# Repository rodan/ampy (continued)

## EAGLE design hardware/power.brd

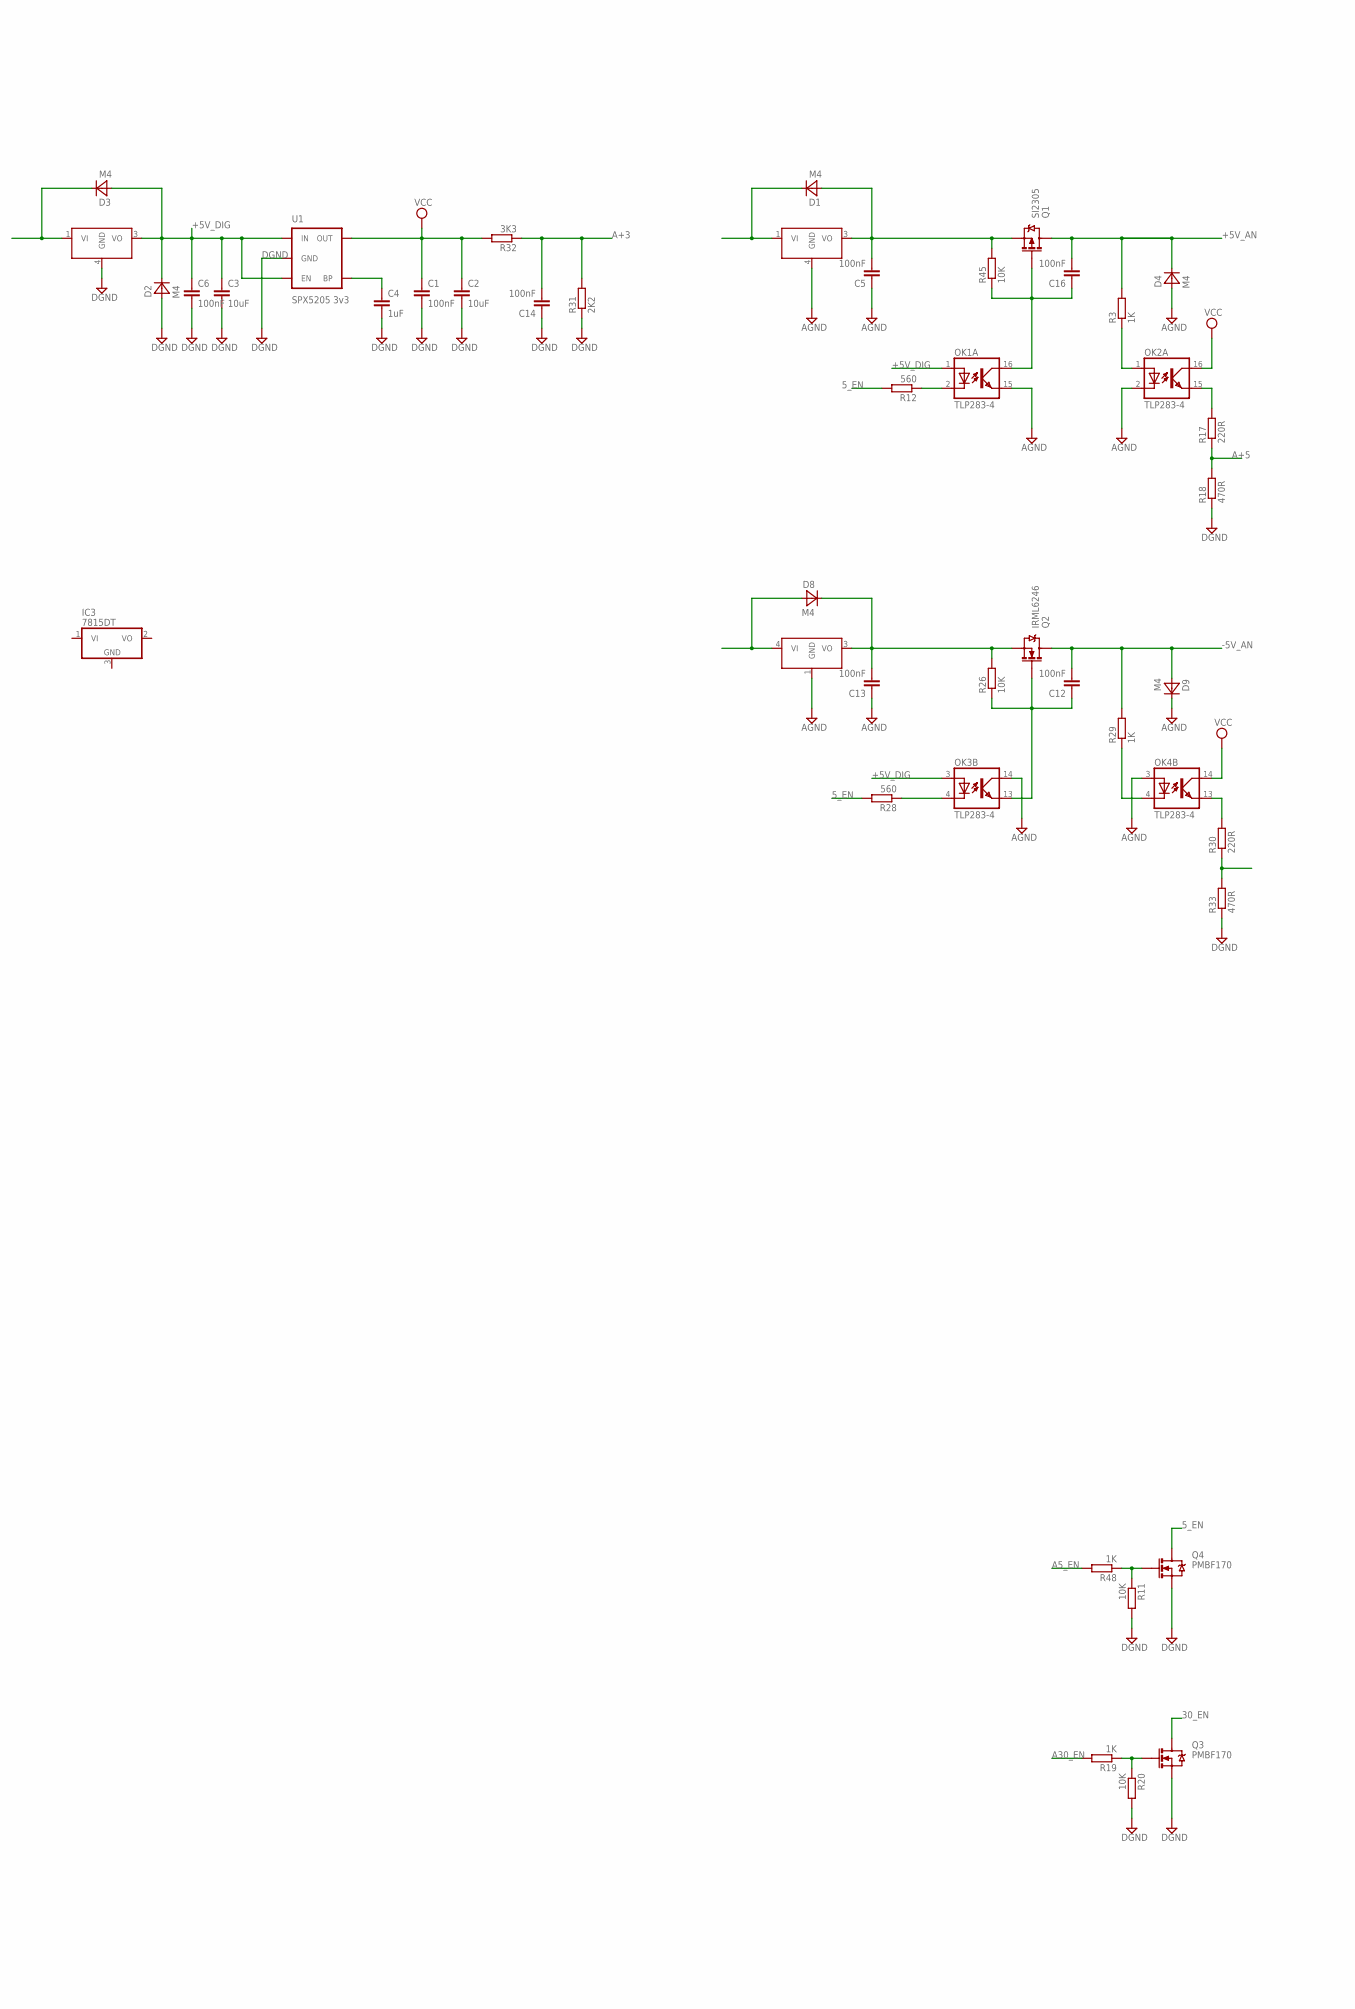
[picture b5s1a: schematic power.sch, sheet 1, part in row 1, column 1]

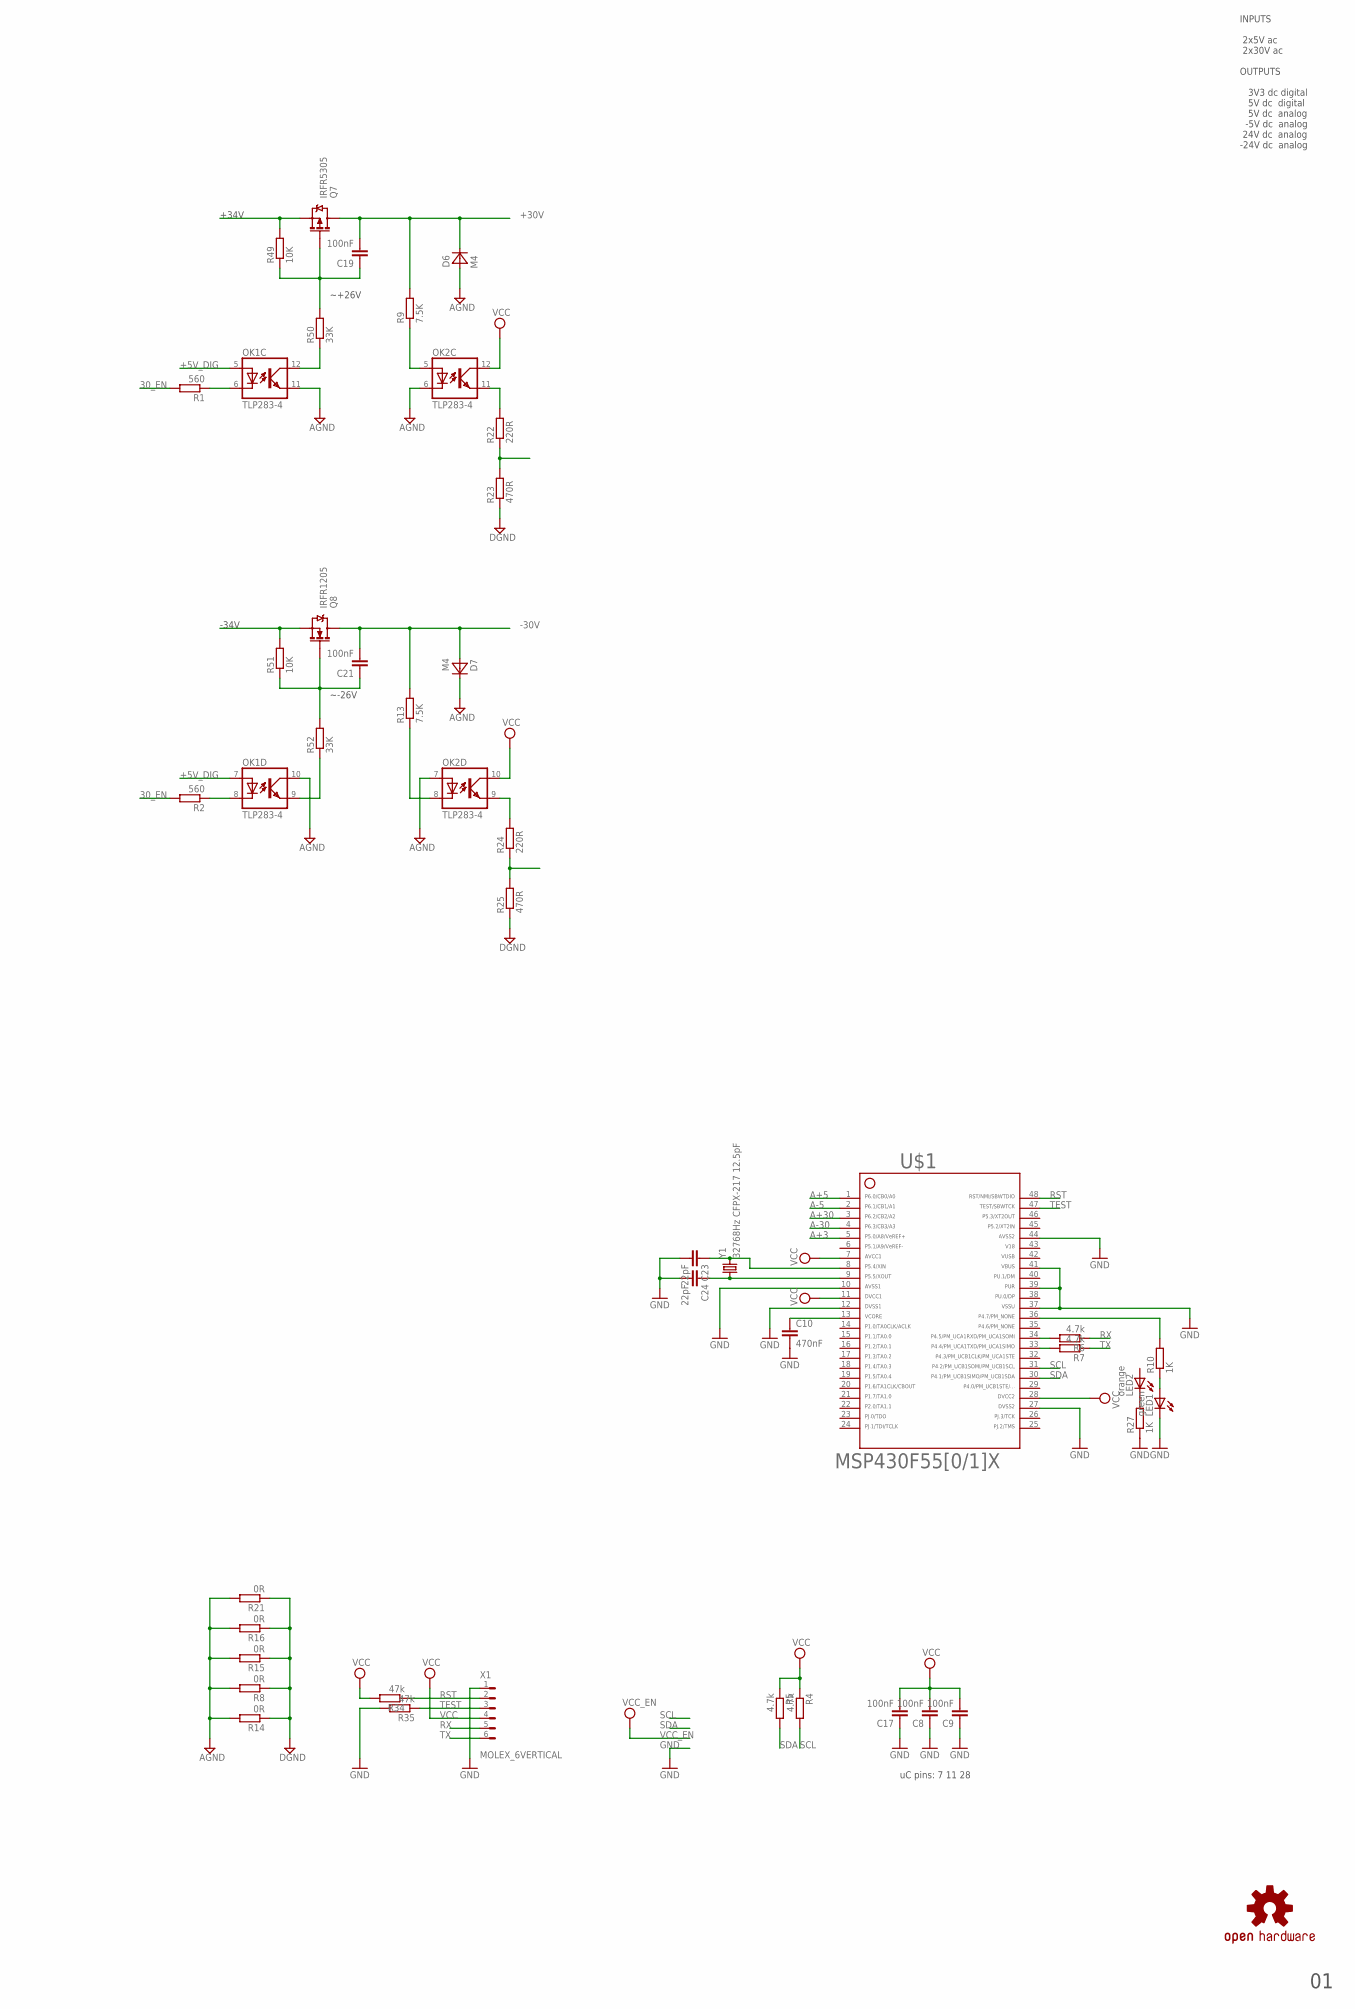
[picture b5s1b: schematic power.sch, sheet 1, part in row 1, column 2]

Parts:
C1, C5, C6, C8, C9, C12, C13, C14, C16, C17, C19, C21: 100nF; C0805
C2, C3: 10uF; C1206
C4: 1uF; C0805
C10: 470nF; C0805
C23, C24: 22pF; C0805
D1, D2, D3, D4, D6, D7, D8, D9: M4; SMA
IC1, IC2: 7805; D2PACK
IC3: 7815DT; TO252
IC4: 7905; D2PACK
LED1: green; CHIP-LED0805
LED2: orange; CHIP-LED0805
OK1, OK2, OK3, OK4: TLP283-4; MINI-FLAT-16
Q1: SI2305; SOT23-3_POWER
Q2: IRML6246; SOT23-3_POWER
Q3, Q4: PMBF170; SOT23-3
Q7: IRFR5305; D-PAK_TO252AA
Q8: IRFR1205; D-PAK_TO252AA
R1, R2, R12, R28: 560; R0805W
R3, R10, R19, R27, R29, R48: 1K; R0805W
R4, R5, R6, R7: 4.7k; R0805W
R8, R14, R15, R16, R21: 0R; R0805W
R9, R13: 7.5K; R0805W
R11, R20, R26, R45, R49, R51: 10K; R0805W
R17, R22, R24, R30: 220R; R0805W
R18, R23, R25, R33: 470R; R0805W
R31: 2K2; R0805W
R32: 3K3; R0805W
R34, R35: 47k; R0805W
R50, R52: 33K; R0805W
U1: SPX5205 3v3; SOT23-5
U$1: F55[0/1]X---PT48; PT48
U$7: OSHW-LOGOM; OSHW-LOGO-M
X1: MOLEX_6VERTICAL; 0530470610
Y1: 32768Hz CFPX-217 12.5pF; CRYSTAL-SMD-3.2X1.5

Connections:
5_EN: Q4.3 (D), R12.2, R28.2
30_EN: Q3.3 (D), R1.2, R2.2
42: U$1.42
43: U$1.43
46: U$1.46
$N2: C13.2, D8.C, IC4.3 (VO), Q2.2 (S), R26.2
$N333: C5.2, D1.A, IC1.3 (VO), Q1.2 (S), R45.2
+5V_AN: C16.2, D4.C, Q1.3 (D), R3.2
+5V_DIG: C3.1, C6.1, D2.C, D3.A, IC2.3 (VO), OK1.1 (A), OK1.5 (A), OK1.7 (A), OK3.3 (A), U1.1 (IN), U1.3 (EN)
+30V: C19.2, D6.C, Q7.2 (D), R9.2
-5V_AN: C12.2, D9.A, Q2.3 (D), R29.2
-30V: C21.2, D7.A, Q8.2 (D), R13.2
A5_EN: R48.2
A30_EN: R19.2
A+3: C14.2, R31.2, R32.1, U$1.5
A+5: R17.1, R18.2, U$1.1
A+30: U$1.3
A-5: U$1.2
A-30: U$1.4
AGND: C5.1, C13.1, D4.A, D6.A, D7.C, D9.C, IC1.4 (GND), IC4.1 (GND), OK1.10 (COL), OK1.11 (EMIT), OK1.15 (EMIT), OK2.2 (C), OK2.6 (C), OK2.7 (A), OK3.14 (COL), OK4.3 (A), R8.2, R14.2, R15.2, R16.2, R21.2
DGND: C1.2, C2.2, C3.2, C4.2, C6.2, C14.1, D2.A, IC2.4 (GND), Q3.2 (S), Q4.2 (S), R8.1, R11.2, R14.1, R15.1, R16.1, R18.1, R20.2, R21.1, R23.1, R25.1, R31.1, R33.1, U1.2 (GND)
GND: C8.1, C9.1, C10.2, C17.1, C23.2, C24.2, LED1.C, R27.1, R35.2, U$1.10, U$1.12, U$1.27, U$1.37, U$1.39, U$1.41, U$1.44, X1.1
LED: R10.2, U$1.36
unnamed: LED1.A, R10.1
unnamed: C4.1, U1.4 (BP)
unnamed: D1.C, IC1.1 (VI)
unnamed: Q4.1 (G), R11.1, R48.1
unnamed: C10.1, U$1.13
unnamed: OK1.2 (C), R12.1
unnamed: OK1.8 (C), R2.1
unnamed: R6.2, U$1.34
unnamed: OK2.1 (A), R3.1
unnamed: R7.2, U$1.33
unnamed: OK2.5 (A), R9.1
unnamed: OK2.8 (C), R13.1
unnamed: Q3.1 (G), R19.1, R20.1
unnamed: OK1.6 (C), R1.1
unnamed: D3.C, IC2.1 (VI)
unnamed: OK2.15 (EMIT), R17.2
unnamed: C12.1, OK3.13 (EMIT), Q2.1 (G), R26.1
unnamed: C24.1, U$1.9, Y1.P$1 (1)
unnamed: C23.1, U$1.8, Y1.P$2 (2)
unnamed: OK2.11 (EMIT), R22.2
unnamed: R22.1, R23.2
unnamed: OK2.9 (EMIT), R24.2
unnamed: R24.1, R25.2
unnamed: D8.A, IC4.4 (VI)
unnamed: OK3.4 (C), R28.1
unnamed: OK4.4 (C), R29.1
unnamed: OK4.13 (EMIT), R30.2
unnamed: R30.1, R33.2
unnamed: C16.1, OK1.16 (COL), Q1.1 (G), R45.1
unnamed: LED2.C, R27.2
unnamed: Q7.3 (S), R49.2
unnamed: C19.1, Q7.1 (G), R49.1, R50.2
unnamed: OK1.12 (COL), R50.1
unnamed: Q8.3 (S), R51.2
unnamed: C21.1, Q8.1 (G), R51.1, R52.2
unnamed: OK1.9 (EMIT), R52.1
RST: R34.1, U$1.48, X1.2
RX: R6.1, X1.5
SCL: R4.2, U$1.31
SDA: R5.2, U$1.30
TEST: R35.1, U$1.47, X1.3
TX: R7.1, X1.6
VCC: C1.1, C2.1, C8.2, C9.2, C17.2, OK2.10 (COL), OK2.12 (COL), OK2.16 (COL), OK4.14 (COL), R4.1, R5.1, R32.2, R34.2, U1.5 (OUT), U$1.7, U$1.11, U$1.28, X1.4

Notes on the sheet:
uC pins: 7 11 28
~+26V
+34V
~-26V
-34V
INPUTS 2x5V ac 2x30V ac OUTPUTS 3V3 dc digital 5V dc digital 5V dc analog -5V dc analog 24V dc analog -24V dc analog

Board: 2 copper layers, 88 parts (0 on the bottom side), 58 nets, no tracks yet.

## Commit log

2014-02-09 add png
2014-02-09 power tweaked
2014-02-09 add msp
2014-02-11 add power module
2014-02-11 cleanup
2014-02-15 change C footprints
2014-02-15 change input filters
2014-02-15 add jumper for pan input
2014-02-15 change input filters - agin
2014-02-16 started routing
2014-04-19 use 7905
2014-04-26 routing
2014-04-28 done routing the mixer
2014-04-28 add amp
2014-04-28 amp update
2014-05-02 amplifier schematic
2014-05-12 mosfets purchased
2014-05-13 amp routed
2014-05-14 add low voltage power source board
2014-05-15 add amp source board
2014-05-15 tweaks
2014-05-20 sent to manufacture
2014-06-02 tweak filters
2014-06-04 small tweaks
2014-06-07 add mixer firmware
2014-06-07 add README
2014-06-08 board rev 1.1
2014-06-08 change +5v bridge rectifier in power_pre
2014-06-15 add firmware for the main uC
2014-06-15 add i2c and uart interfaces
2014-06-16 works part1
2014-06-17 s/sprintf/snprintf/g
2014-06-18 code cleanup
2014-06-23 use non-blocking delays and LPM3
2014-07-03 add pic link
2014-07-03 add display firmware
2014-07-03 fix indent
2014-12-17 add pinout
2014-12-17 add UI, sound detection
2014-12-18 add debounce and timeouts for sound detection routine
2014-12-19 ir_isr tied in directly not thru the sys_messagebus
2014-12-19 remove ir debug
2014-12-19 new power amp
2014-12-20 switch to i2c bitbang, implelent clock stretching
2014-12-24 add linux client
2014-12-24 add ncurses
2014-12-28 borrow code from alsamixer
2014-12-28 borrow some more
2014-12-28 cleanup, fix for screen resize
2014-12-31 store_registers() added
2014-12-31 lm4780_helper added
2014-12-31 new year cleanup
2014-12-31 change labels
2015-01-02 add internal tty reconf and transmit buffers
2015-01-02 add autotools
2015-01-02 use compile time default stty
2015-01-02 add replies
2015-01-02 ampy_tx_cmd now expects the length of the reply
2015-01-03 move sources to src
2015-01-03 add gitignore
2015-01-03 flush file descriptor buffer before every new command
2015-01-04 automake added
2015-01-04 remove m4 dir dependency
2015-01-04 remove m4 dir dependency part2
2015-01-04 bootstrap updated
2015-01-04 add ebuild
2015-01-04 repoman fixes
2015-01-22 fix gnd_c in amp_lm4780
2015-01-23 add buffer to snd detect circuit
2015-01-27 spice simulation added
2015-01-27 redesign snd_detect circuit layout
2015-01-28 snd_detect cleanup
2015-01-29 snd_detect revisited
2015-02-12 add xor hashes to serial comms
2015-02-12 add temperature sensing
2015-02-12 add missing files
2015-02-16 add temperature reading inside the mixer board
2015-02-17 add debug window into ncurses cli
2015-02-18 add hash to showreg
2015-03-10 delay get_mixer_status during init
2015-03-28 amp tests
2015-03-28 power down amps when there is no active channel driving them
2015-06-21 fix segfault when unknown command line option is sent
2016-12-11 new bootstrap scripts
2018-12-13 change email address
2018-12-13 photo link changed
